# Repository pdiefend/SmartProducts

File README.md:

# SmartProducts
SmartProducts (The IoT) side of the 147 Lab Repo. Also in the process of migrating from Google Code as well as merging with an offline repo.

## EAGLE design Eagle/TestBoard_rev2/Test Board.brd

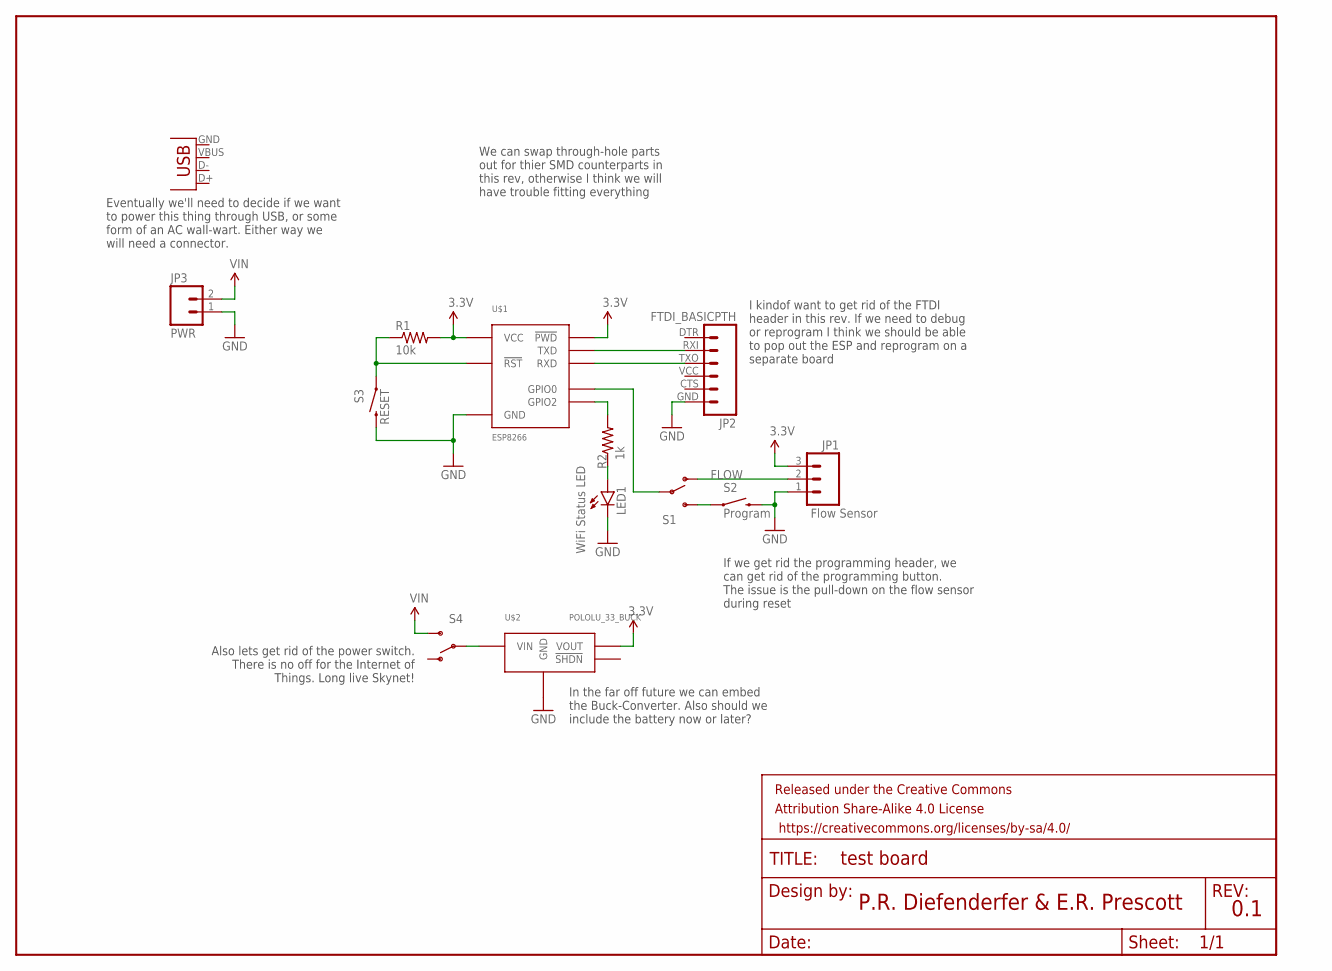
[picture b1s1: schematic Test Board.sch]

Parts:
FRAME1: FRAME-LETTER; CREATIVE_COMMONS
JP1: Flow Sensor; 1X03_LOCK
JP2: FTDI_BASICPTH; FTDI_BASIC
JP3: PWR; 1X02_LOCK
JP4: USBSMD; USB-MINIB
LED1: WiFi Status LED; LED3MM-NS
R1: 10k; AXIAL-0.3
R2: 1k; AXIAL-0.3
S1, S4: SWITCH-SPDTPTH; SWITCH-SPDT
S2: Program; TACTILE-PTH
S3: RESET; TACTILE-PTH
U$1: ESP8266; 2X4_LOCK
U$2: POLOLU_33_BUCK; 1X4_LOCK

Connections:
3.3V: JP1.3, R1.P$2 (2), U$1.CH_PD (!PWD), U$1.VCC, U$2.VOUT
FLOW: JP1.2, S1.1 (O)
GND: JP1.1, JP2.GND (6), JP3.1, LED1.K (C), S2.3 (2), S3.3 (2), U$1.GND, U$2.GND
unnamed: S1.3 (S), S2.1
unnamed: JP2.RXI (2), U$1.TXD
unnamed: R1.P$1 (1), S3.1, U$1.RST (!RST)
unnamed: JP2.TXO (3), U$1.RXD
unnamed: LED1.A, R2.P$1 (1)
unnamed: R2.P$2 (2), U$1.GPIO2
unnamed: S1.2, U$1.GPIO0
unnamed: S4.2, U$2.VIN
VIN: JP3.2, S4.3 (S)

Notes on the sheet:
P.R. Diefenderfer & E.R. Prescott
0.1
Eventually we'll need to decide if we want to power this thing through USB, or some form of an AC wall-wart. Either way we will need a connector.
We can swap through-hole parts out for thier SMD counterparts in this rev, otherwise I think we will have trouble fitting everything
I kindof want to get rid of the FTDI header in this rev. If we need to debug or reprogram I think we should be able to pop out the ESP and reprogram on a separate board
Also lets get rid of the power switch. There is no off for the Internet of Things. Long live Skynet!
In the far off future we can embed the Buck-Converter. Also should we include the battery now or later?
If we get rid the programming header, we can get rid of the programming button. The issue is the pull-down on the flow sensor during reset

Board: 2 copper layers, 14 parts (0 on the bottom side), 12 nets, no tracks yet.

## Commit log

2015-03-16 Actual First commit of PRD's code from GCode
    Arduino code for the ESP that includes the first tests of the ESP
    module. More code will come soon from the Native SDK.
2015-03-16 Actual First Commit try 2
    Committing what will be the folder containing the workspace for the
    Native ESP SDK.
2015-03-16 Adding files from computer with SDK
2015-03-17 added new interrupt project and cleaned temp files
2015-03-17 Basic interruptCounter example works
2015-03-18 Interrupt Counter works with thingspeak. Code Uncommented
2015-03-19 WiFi stat LED works, Code better commented
2015-03-19 Modified gitignore to ignore user_config.h on all new projects. Don't put anything you want shared up there
2015-03-20 Added SDK programming Guide. I thought the Guide was already included here. This may cause a mess on my laptop.
2015-03-21 Upgraded to SDK v1.0.0 (Relased Today!) There is not much along the lines of code changes in this commit, only an SDK and compiler upgrade to the latest SDK version. All existing projects for the ESP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
2015-03-21 Forgot to stage some changes in last commit. Sorry.
2015-03-22 Modified the Interrupt Counter program to only send data when new The Interrupt Counter now only sends all of the button presses between periods of being pressed (when the button is pressed it cumula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
2015-04-13 Modified Interrupt Counter code to convert the pulse edges to mL and added an extra digit to data to be sent.
2015-04-18 Added new IoToliets Project and added some thoughts on implementation of the event recognition.
2015-04-27 Added a Comment about Something
    I'm here!!!
2015-04-28 Added Eagle Drawing for Circuit
    It's a schematic for the test setup employed thus far. Packages are NOT
    picked for a board, and this should be treated only as a schematic.
    Ideally it will get updated with a better ESP symbol.
2015-04-28 I don't like your organization Ward...
    Moved the Eagle Schematic to a better spot for organization purposes and
    Rearranged the schematic while adding some labels to better suit style
    guidelines for readability.
2015-04-30 Rev 0.1 Carrier Board ready for Proto-Run
    The Rev 0.1 Carrier board is just about ready for a prototype run on the
    PCB mill and is designed for a mill with no silk or solder mask. Changes
    include an edited schematic to include a better ESP part. power
    considerations, and some formatting for readability. A first-run
    mill-able board has been prepared as well. Finally, the Git Ignore was
    modified to ignore temporary Eagle Files.
2015-05-01 Added Rev2 of the prototype PCB
    Added a second revision that has a better form factor that can be better
    mounted on the Flow sensor. The board needs to be laid out and there are
    some design decisions that also need to be made.
2015-06-29 Initial commit for new Enphase RTD project and LMP projects. EnphaseRTD project is not working most likely due to SSL and I am going to attempt to update the SDK version to see if the problems go awa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
2015-06-29 EnphaseRTD still does not work. All I get is HTTP 400 Bad Request, no matter what I try. I think SSL is working, but I can't find an error in the HTTP requests so I am unsure as to what the culprit i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
2015-06-29 Got Curl to work with confirmed IP address and Port. Try coping the Request tomorrow?
2015-06-30 Enphase Downloading (kindof) works. Data is received. Next step is to implement smarter connections and downloading so we don't keep a persistent connection to the server then work on parsing the JSO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
2015-06-30 Modified program so it only connects when it wants to make a request. Current the connection is terminated when an unknown error occurs, so I guess I;m leaving it that way. Code also parses out the c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
2015-06-30 Working on the WS2812B interface. The timing needs some serious help
2015-06-30 Fuck it. See you guys at the bar.
2015-07-01 Got GPIO figured out. Issue with oscillations was due to oddity at boot (bootload is partially to blame) combined with incorrect GPIO settings. Other uncommited issue of GPIO speed was (sort of) reso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
2015-07-03 Still trying to get the timing right on the WS2812 LED. This is starting to get annoying. Maybe it has to do with the voltage levels?

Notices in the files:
parts and their libraries:
SparkFun-Aesthetics: Licensing: Creative Commons ShareAlike 4.0 International - https://creativecommons.org/licenses/by-sa/4.0
SparkFun-Aesthetics: Released under the Creative Commons Attribution Share-Alike 4.0 License
SparkFun-Aesthetics: https://creativecommons.org/licenses/by-sa/4.0
